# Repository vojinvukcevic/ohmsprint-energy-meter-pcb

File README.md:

# Bluetooth Energy Meter PCB (OhmSprint 2026)

Hardware design of a single-phase **energy meter with Bluetooth Low Energy and USB**, built around the Microchip **ATM90E26** metering IC and an **STM32F373** microcontroller. Designed in **KiCad** by a team for **OhmSprint 2026**, a student hardware competition organized by **Meter&Control** in Belgrade.

**Result:** out of about 40 teams, the design was selected as one of the **10 finalists** whose boards were manufactured and assembled by the organizer. The final stage was board bring-up, firmware testing and verification of measurement accuracy on site.

| PCB layout (F.Cu red, B.Cu blue) | Schematic |
|---|---|
|  | [Open the schematic (PDF)](docs/OhmSprint_V1_schematic.pdf) |

---

## Contents

- [The task](#the-task)
- [My role](#my-role)
- [Hardware architecture](#hardware-architecture)
- [PCB](#pcb)
- [What I would improve in a V2](#what-i-would-improve-in-a-v2)
- [Repository layout](#repository-layout)

---

## The task

Design a device based on the **ATM90E26** metering chip and a microcontroller of our choice that precisely measures:

- RMS voltage and RMS current,
- line frequency,
- instantaneous active power,
- consumed active energy,

and presents the results through an interface of our choice (on-device display, or wired/wireless transfer to a phone or PC).

**Hardware requirements and how the design meets them:**

| Requirement | This design |
|---|---|
| Voltage input: secondary of a mains transformer, approx. 7 V RMS, via a **PJ-002AH-SMT-TR** connector | J1 = PJ-002AH; the same secondary also powers the board (allowed by the task) |
| Current measurement with an **SCT013** current transformer via an **SJ-3523-SMT-TR** connector | J2 = SJ-3523 3.5 mm jack, with burden resistors and an RC anti-aliasing filter |
| Schematic and PCB in **KiCad** | KiCad 10 |
| **2-layer** PCB, max. **15 × 15 cm** | 2 layers, **84.4 × 68.9 mm** |
| Smallest component size **0603** | No part smaller than 0603; most passives are 0805 |
| Organizer's design rules (0.1 mm clearance/track, 0.35 mm min. via, 0.3 mm copper-to-edge, …) | Entered exactly as given in the KiCad board setup, so DRC checks against them |
| Outputs: Gerbers (11 layers), drill files, BOM with MPN and manufacturer | [`fabrication/`](fabrication/), [`bom/`](bom/) |
| Total BOM cost **≤ 50 EUR**, parts from DigiKey | Parts selected from DigiKey |

---

## My role

Team of four: three hardware engineers and one developer who built the phone app.

- **Schematic:** drew almost the entire schematic (power supply, ATM90E26 metering front end, MCU, USB-C and BLE sections).
- **Component selection:** chose the main parts with the team; see [design decisions](#design-decisions).
- **PCB layout:** shared component placement and routing with one teammate.
- **Libraries:** imported and integrated the manufacturer symbols, footprints and 3D models.
- **Fabrication outputs:** generated the Gerber files, drill files and BOM with the team.

---

## Hardware architecture

```mermaid
flowchart LR
    TR["Mains transformer<br/>~7 V AC (J1)"] -->|half-wave rectifier<br/>1N4007 + bulk caps| LDO["AP2213<br/>3.3 V LDO"]
    TR -->|resistor divider| ATM
    CT["SCT013 current<br/>transformer (J2)"] -->|burden + RC filter| ATM["ATM90E26<br/>metering IC"]
    ATM -->|SPI + IRQ, ZX,<br/>WarnOut, CF1/CF2| MCU["STM32F373<br/>MCU"]
    MCU -->|USART2 + RTS/CTS| BLE["BM70<br/>BLE module"]
    MCU -->|USB FS| USB["USB-C<br/>(J3)"]
    LDO --> MCU & ATM & BLE
```

| Block | Part | Notes |
|---|---|---|
| Metering | **ATM90E26** (Microchip) | Required by the task. 8.192 MHz crystal, SPI to the MCU; IRQ, zero-crossing (ZX), WarnOut and energy pulse outputs (CF1/CF2, also drive LEDs) |
| MCU | **STM32F373CCT6** (ST) | Arm Cortex-M4F; SPI master to the ATM90E26, USART2 with hardware flow control to the BLE module, USB full-speed device |
| Wireless | **BM70** (Microchip) | Bluetooth LE module for sending measurements to a phone; copper cutout under the antenna; mode and reset controlled from the MCU |
| Power | **AP2213-3.3** LDO | 3.3 V rail from the half-wave rectified transformer voltage (1N4007, 220 µF + 100 µF bulk) |
| USB | **USB4105** USB-C receptacle, **USBLC6-2SC6** ESD protection | 22 Ω series resistors on D+/D−, 1.5 kΩ D+ pull-up, 5.1 kΩ CC pull-downs (sink) |
| User I/O | 5 slide switches, 4 LEDs | Switches set the ATM90E26 configuration pins, STM32 BOOT0 and the BM70 mode |

Full parts list with manufacturer part numbers: [`bom/OhmSprint_V1_BOM.csv`](bom/OhmSprint_V1_BOM.csv).

### Design decisions

- **STM32F373 as the MCU:** a Cortex-M4 with a hardware floating-point unit for processing the measurement data, from an STM32 line that ST positions for precision analog measurement applications.
- **BM70 for Bluetooth LE:** we chose wireless transfer to a phone as the more challenging option for presenting the results. The BM70 is a complete BLE module controlled over a simple UART interface, so the MCU only needs to send data over serial instead of running a BLE stack.
- **LDO instead of a switching converter:** the board only needs a single 3.3 V rail at low current, so a linear regulator (AP2213) after the rectifier gives a simpler, low-noise supply with fewer parts and no switching layout concerns near the measurement front end.

---

## PCB

| | |
|---|---|
| Layers | 2 (F.Cu, B.Cu) |
| Size | 84.4 × 68.9 mm |
| Thickness | 1.6 mm |
| Ground | GND pour on both layers |
| Mounting | 4 × mounting holes |
| Tool | KiCad 10 |

**Design notes:**
- The BLE module sits at the board edge with a cutout under its antenna, so no copper detunes it.
- The STM32 analog supply (VDDA) is filtered from the 3.3 V rail through a ferrite bead.
- USB data lines run from the connector through the ESD protection IC and the series resistors to the MCU.
- The measurement inputs (transformer and current-transformer jacks) enter on the left edge; the BLE module sits on the opposite edge.

---

## What I would improve in a V2

- **Debug header:** route the STM32 SWD pins (SWDIO, SWCLK) together with NRST and GND to a small header, so the MCU can be programmed and debugged with a standard probe instead of only through the BOOT0 bootloader.
- **Test points:** add test points on the 3.3 V rail, the rectified input and the SPI and UART lines, to make bring-up measurements with an oscilloscope and multimeter faster.
- **USB power:** connect USB-C VBUS so the digital part (MCU, BLE) can be powered and programmed from a laptop without the mains transformer connected.

---

## Repository layout

```
├── README.md
├── kicad/                       # KiCad 10 project
│   ├── OhmSprint_V1.kicad_pro
│   ├── OhmSprint_V1.kicad_sch
│   ├── OhmSprint_V1.kicad_pcb
│   ├── Symbols/                 # imported manufacturer symbols
│   ├── Footprints/              # imported manufacturer footprints
│   └── 3D_models/               # STEP models
├── fabrication/
│   ├── gerbers/                 # Gerber files (2 layers)
│   └── drill/                   # PTH and NPTH drill files
├── bom/OhmSprint_V1_BOM.csv
└── docs/
    ├── OhmSprint_V1_schematic.pdf
    └── img/
        ├── pcb_3d.png           # 3D view of the assembled board
        └── pcb_layout.png       # copper layout, both layers
```

To open the project, install **KiCad 10** and open `kicad/OhmSprint_V1.kicad_pro`.

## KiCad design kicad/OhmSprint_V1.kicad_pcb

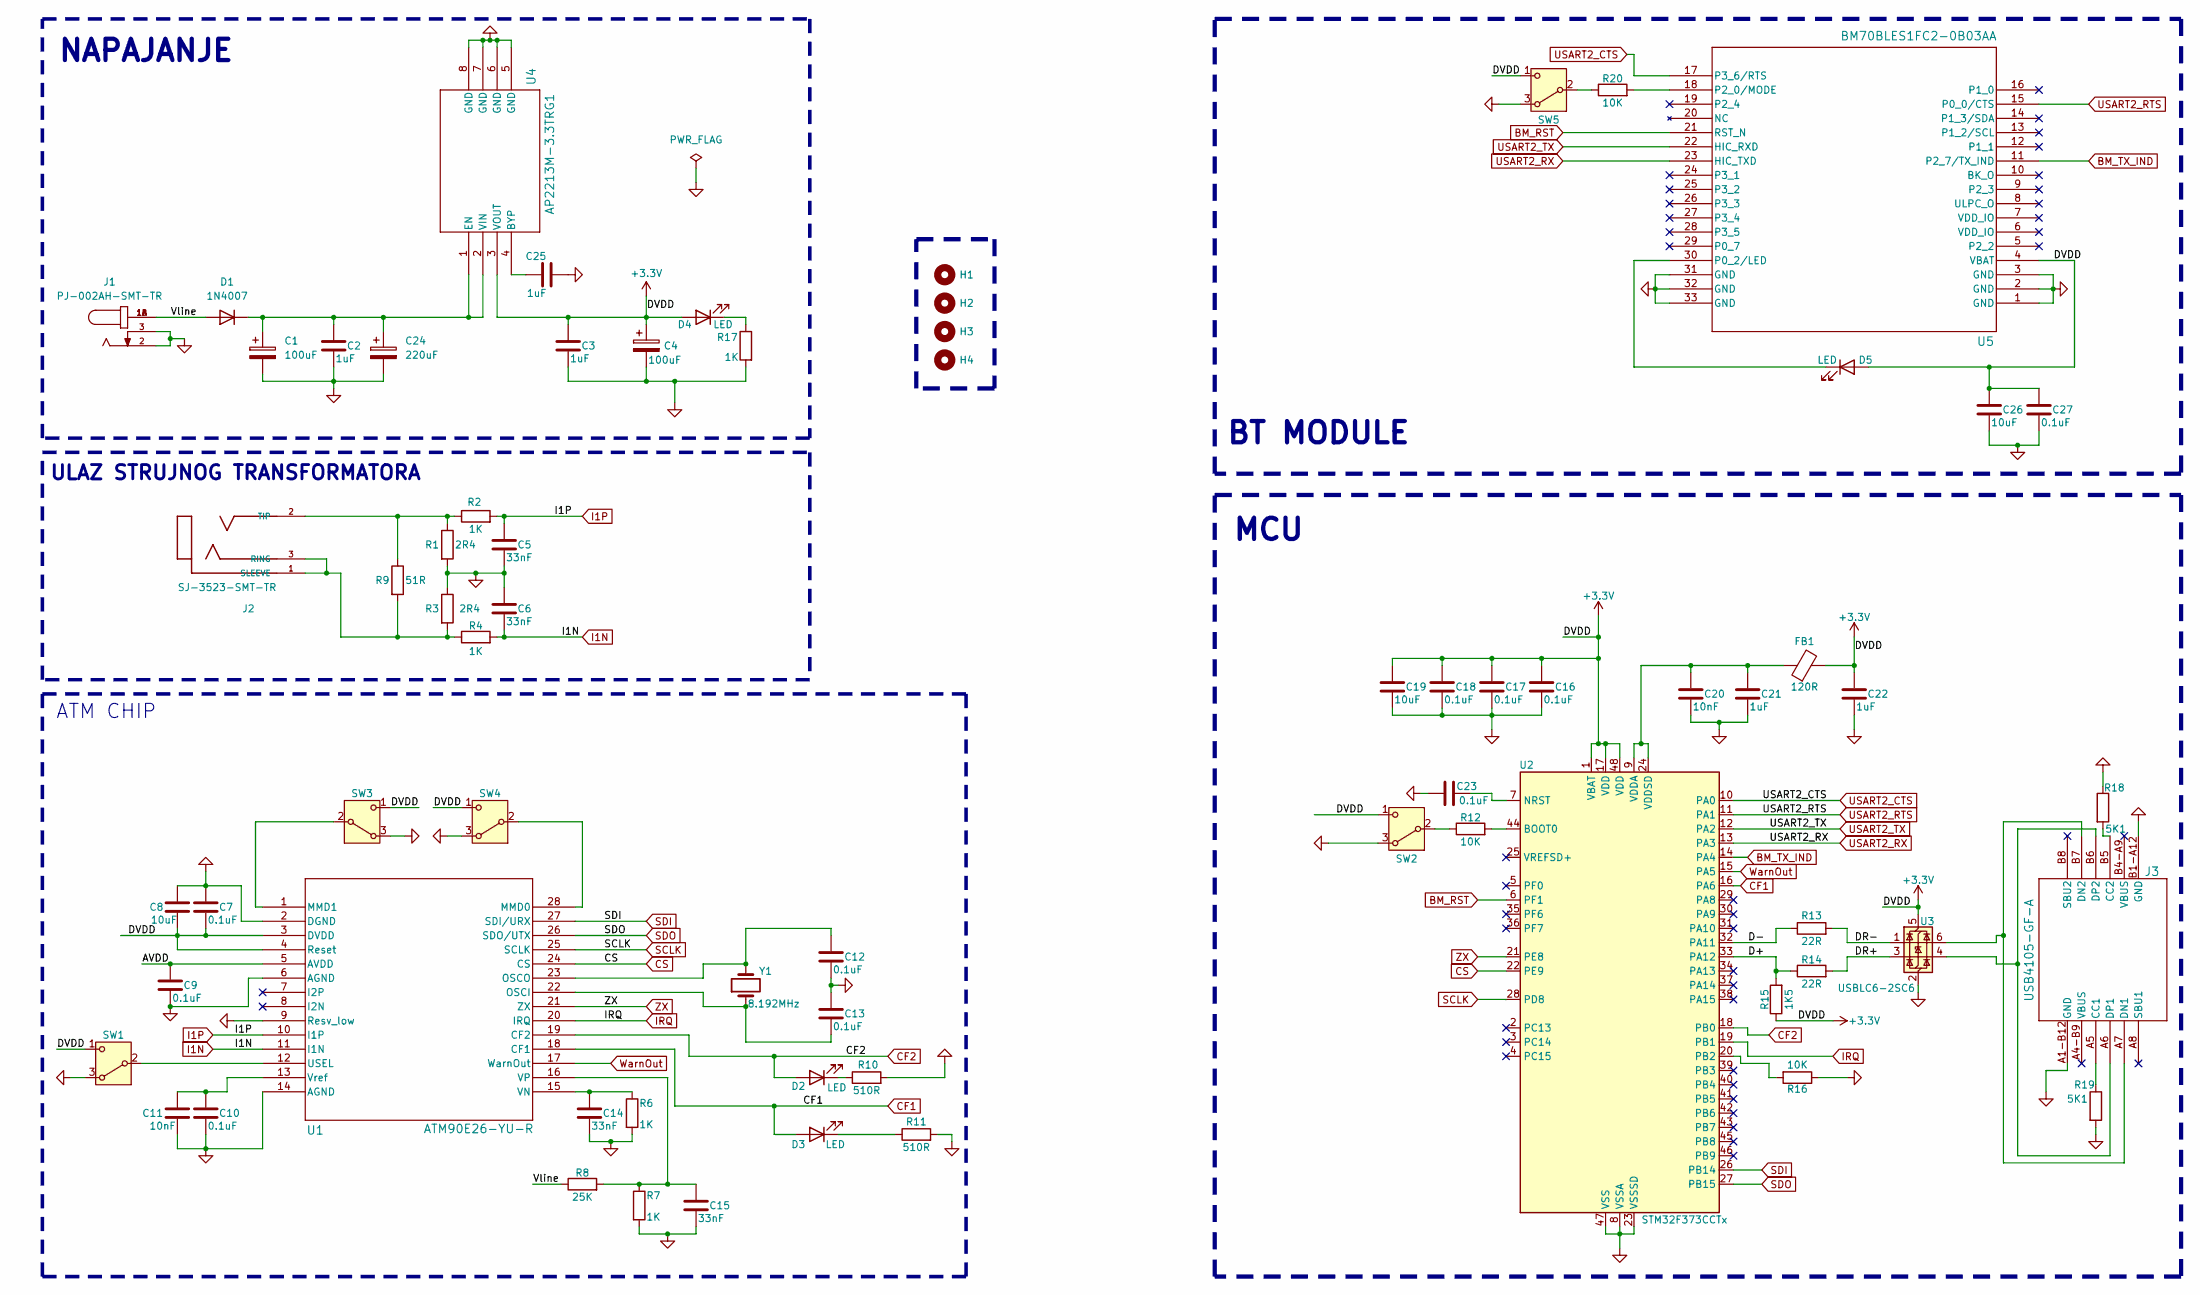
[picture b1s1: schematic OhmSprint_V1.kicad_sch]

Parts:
C1, C4: 100uF; 100uF_Polarized_Cap
C2, C3, C21, C22, C25: 1uF; 1uF_Cap
C5, C6, C14, C15: 33nF; 33nF_Cap
C7, C9, C10, C12, C13, C16, C17, C18, C23, C27: 0.1uF; 0.1uF_Cap
C8, C19, C26: 10uF; 10uF_Cap
C11: 10nF; 10nF_Cap
C20: 10nF; 10uF_Cap
C24: 220uF; 220uF_Polarized_Cap
D1: 1N4007; DIO_N4007-T_DIO
D2, D3, D4, D5: LED; LED_0805_2012Metric
FB1: 120R; FB_LI0805H121R-10
H1, H2, H3, H4: MountingHole; MountingHole_2.1mm
J1: PJ-002AH-SMT-TR; CUI_PJ-002AH-SMT-TR
J2: SJ-3523-SMT-TR; CUI_SJ-3523-SMT-TR
J3: USB4105-GF-A; USB4105_GCT
R1, R3: 2R4; 2R4_Resistor
R2, R4, R6, R7, R17: 1K; 1K_Resistor
R8: 25K; 25K_Resistor
R9: 51R; 51R_Resistor
R10, R11: 510R; 510R_Resistor
R12, R20: 10K; 10K_Resistor
R13, R14: 22R; 22R_Resistor
R15: 1K5; 1K5_Resistor
R16: 10K; 1K5_Resistor
R18, R19: 5K1; 5K1_Resistor
SW1, SW2, SW3, SW4, SW5: SW_Nidec_CAS-120A1; SW_EG1218
U1: ATM90E26-YU-R; ATM90E26
U2: STM32F373CCTx; STM32F373CCT6
U3: USBLC6-2SC6; USBLC6-25C6
U4: AP2213M-3.3TRG1
U5: BM70BLES1FC2-0B03AA; BM70BLES1FC2_MCH
Y1: 8.192MHz; CRYSTAL-AA-8.192MAGE

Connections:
+3.3V: C3.1, C4.1, C7.2, C8.2, C16.1, C17.1, C18.1, C19.1, C22.1, C26.1, C27.1, D4.2 (A), D5.2 (A), FB1.2, R15.1, SW1.1 (C), SW2.1 (C), SW3.1 (C), SW4.1 (C), SW5.1 (C), U1.3 (DVDD), U1.4 (Reset), U2.1 (VBAT), U2.17 (VDD), U2.48 (VDD), U3.5 (VBUS), U4.3 (VOUT), U5.4 (VBAT)
/AVDD: C9.1, U1.5 (AVDD)
/D+: R14.1, R15.2, U2.33 (PA12)
/D-: R13.1, U2.32 (PA11)
/DR+: R14.2, U3.3 (I/O2)
/DR-: R13.2, U3.1 (I/O1)
/Vline: D1.2 (A), J1.1A, J1.1B, R8.1
BM_RST: U2.6 (PF1), U5.21 (RST_N)
BM_TX_IND: U2.14 (PA4), U5.11 (P2_7/TX_IND)
CF1: D3.2 (A), U1.18 (CF1), U2.16 (PA6)
CF2: D2.2 (A), U1.19 (CF2), U2.18 (PB0)
CS: U1.24 (CS), U2.22 (PE9)
GND: C1.2, C2.2, C3.2, C4.2, C5.2, C6.1, C7.1, C8.1, C9.2, C10.2, C11.2, C12.2, C13.1, C14.2, C15.2, C16.2, C17.2, C18.2, C19.2, C20.2, C21.2, C22.2, C23.1, C24.2, C25.2, C26.2, C27.2, J1.2, J1.3, J3.A1-B12 (GND), J3.B1-A12 (GND), R1.2, R3.1, R6.2, R7.2, R10.2, R11.2, R16.1, R17.2, R18.1, R19.2, SW1.3 (A), SW2.3 (A), SW3.3 (A), SW4.3 (A), SW5.3 (A), U1.2 (DGND), U1.6 (AGND), U1.9 (Resv_low), U1.14 (AGND), U2.8 (VSSA), U2.23 (VSSSD), U2.47 (VSS), U3.2 (GND), U4.5 (GND), U4.6 (GND), U4.7 (GND), U4.8 (GND), U5.1 (GND), U5.2 (GND), U5.3 (GND), U5.31 (GND), U5.32 (GND), U5.33 (GND)
I1N: C6.2, R4.2, U1.11 (I1N)
I1P: C5.1, R2.2, U1.10 (I1P)
IRQ: U1.20 (IRQ), U2.19 (PB1)
unnamed: C1.1, C2.1, C24.1, D1.1 (K), U4.1 (EN), U4.2 (VIN)
unnamed: D2.1 (K), R10.1
unnamed: D3.1 (K), R11.1
unnamed: D4.1 (K), R17.1
unnamed: D5.1 (K), U5.30 (P0_2/LED)
unnamed: J2.1 (SLEEVE), J2.3 (RING), R3.2, R4.1, R9.2
unnamed: J2.2 (TIP), R1.1, R2.1, R9.1
unnamed: J3.A5 (CC1), R19.1
unnamed: J3.B5 (CC2), R18.2
unnamed: J3.A7 (DN1), J3.B7 (DN2), U3.6 (I/O1)
unnamed: J3.A6 (DP1), J3.B6 (DP2), U3.4 (I/O2)
unnamed: SW1.2 (B), U1.12 (USEL)
unnamed: R12.1, SW2.2 (B)
unnamed: SW3.2 (B), U1.1 (MMD1)
unnamed: SW4.2 (B), U1.28 (MMD0)
unnamed: R20.1, SW5.2 (B)
unnamed: C13.2, U1.22 (OSCI), Y1.1
unnamed: C12.1, U1.23 (OSCO), Y1.2
unnamed: C14.1, R6.1, U1.15 (VN)
unnamed: C15.1, R7.1, R8.2, U1.16 (VP)
unnamed: C10.1, C11.1, U1.13 (Vref)
unnamed: R12.2, U2.44 (BOOT0)
unnamed: C23.2, U2.7 (NRST)
unnamed: R16.2, U2.20 (PB2)
unnamed: C20.1, C21.1, FB1.1, U2.9 (VDDA), U2.24 (VDDSD)
unnamed: C25.1, U4.4 (BYP)
unnamed: R20.2, U5.18 (P2_0/MODE)
SCLK: U1.25 (SCLK), U2.28 (PD8)
SDI: U1.27 (SDI/URX), U2.26 (PB14)
SDO: U1.26 (SDO/UTX), U2.27 (PB15)
USART2_CTS: U2.10 (PA0), U5.17 (P3_6/RTS)
USART2_RTS: U2.11 (PA1), U5.15 (P0_0/CTS)
USART2_RX: U2.13 (PA3), U5.23 (HIC_TXD)
USART2_TX: U2.12 (PA2), U5.22 (HIC_RXD)
WarnOut: U1.17 (WarnOut), U2.15 (PA5)
ZX: U1.21 (ZX), U2.21 (PE8)

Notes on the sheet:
NAPAJANJE
ATM CHIP
BT MODULE
ULAZ STRUJNOG TRANSFORMATORA
MCU

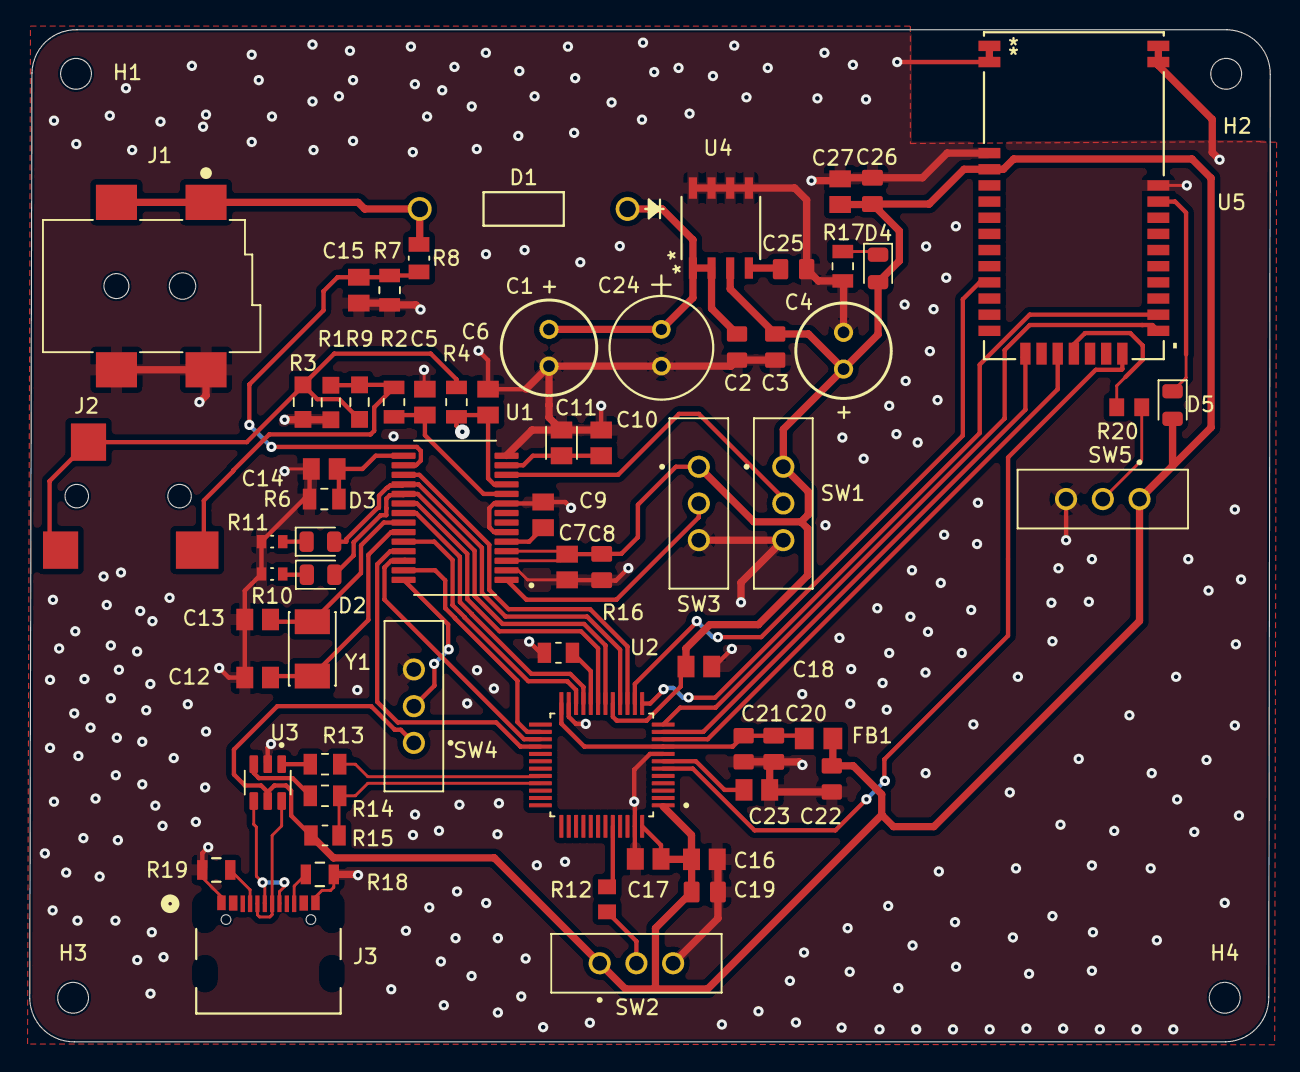
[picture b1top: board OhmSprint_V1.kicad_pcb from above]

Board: 2 copper layers, 84.4 x 68.9 mm, 70 parts (0 on the bottom side), 52 nets.

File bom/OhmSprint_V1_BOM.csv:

"Reference","Qty","Value","Exclude from BOM","Datasheet","MANUFACTURER","Manufacturer Product Number"
"C1,C4","2","100uF","","https://www.digikey.com/en/products/detail/w%C3%BCrth-elektr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","Würth Elektronik","860040573004"
"C2,C3,C21,C22,C25","5","1uF","","https://www.digikey.com/en/products/detail/samsung-electro-m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","Samsung Electro-Mechanics","CL21B105KAFNNNE"
"C5,C6,C14,C15","4","33nF","","https://www.digikey.com/en/products/detail/tdk/C2012C0G1H333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","TDK","C2012C0G1H333J125AA"
"C7,C9,C10,C12,C13,C16,C17,C18,C23,C27","10","0.1uF","","https://www.digikey.com/en/products/detail/kemet/C0805C104K5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","KEMET","C0805C104K5RACTU"
"C8,C19,C26","3","10uF","","https://www.digikey.com/en/products/detail/samsung-electro-m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","Samsung Electro-Mechanics","CL21A106KOQNNNE"
"C11,C20","2","10nF","","https://www.digikey.com/en/products/detail/kemet/C0805C103K5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","KEMET","C0805C103K5RACTU"
"C24","1","220uF","","https://www.digikey.com/en/products/detail/rubycon/25YXJ220M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","Rubycon","25YXJ220M6.3X11"
"D1","1","1N4007","","https://www.digikey.com/en/products/detail/mcc-micro-commerc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","MCC (Micro Commercial Components)","1N4007-TP"
"D2,D3,D4,D5","4","LED","","https://www.digikey.com/en/products/detail/xinglight/XL-2012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","XINGLIGHT","XL-2012UGC"
"FB1","1","120R","","https://www.digikey.com/en/products/detail/laird-signal-inte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","Laird-Signal Integrity Products","LI0805H121R-10"
"J1","1","PJ-002AH-SMT-TR","","https://www.digikey.com/en/products/detail/same-sky-formerly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","Same Sky (Formerly CUI Devices)","PJ-002AH-SMT-TR"
"J2","1","SJ-3523-SMT-TR","","https://www.digikey.com/en/products/detail/same-sky-formerly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","Same Sky (Formerly CUI Devices)","SJ-3523-SMT-TR"
"J3","1","USB4105-GF-A","","https://www.digikey.com/en/products/detail/gct/USB4105-GF-A/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","GCT","USB4105-GF-A"
"R1,R3","2","2R4","","https://www.digikey.com/en/products/detail/panasonic-industr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","Panasonic Industry","ERJ-6GEYJ2R4V"
"R2,R4,R6,R7,R17","5","1K","","https://www.digikey.com/en/products/detail/vishay-dale/CRCW0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","Vishay Dale","CRCW08051K00FKEA"
"R8","1","25K","","https://www.digikey.com/en/products/detail/te-connectivity-p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","TE Connectivity Passive Product","CPF0805B25KE1"
"R9","1","51R","","https://www.digikey.com/en/products/detail/panasonic-industr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","Panasonic Industry","ERJ-P06F51R0V"
"R10,R11","2","510R","","https://www.digikey.com/en/products/detail/panasonic-industr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","Panasonic Industry","ERJ-3GEYJ511V"
"R12,R16,R20,R21","4","10K","","https://www.digikey.com/en/products/detail/yageo/RT0805BRD07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","YAGEO","RT0805BRD0710KL"
"R13,R14","2","22R","","https://www.digikey.com/en/products/detail/vishay-dale/CRCW0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","Vishay Dale","CRCW080522R0FKEA"
"R15","1","1K5","","https://www.digikey.com/en/products/detail/yageo/RC0805FR-07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","YAGEO","RC0805FR-071K5L"
"R18,R19","2","5K1","","https://www.digikey.com/en/products/detail/koa-speer-electro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","KOA Speer Electronics, Inc.","RK73B2ATTD512J"
"SW1,SW2,SW3,SW4,SW5","5","SW_Nidec_CAS-120A1","","https://www.digikey.com/en/products/detail/e-switch/EG1218/101726","E-Switch","EG1218"
"U1","1","ATM90E26-YU-R","","https://www.digikey.com/en/products/detail/microchip-technol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","Microchip Technology","ATM90E26-YU-R"
"U2","1","STM32F373CCTx","","https://www.digikey.com/en/products/detail/stmicroelectronic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","STMicroelectronics","STM32F373CCT6"
"U3","1","USBLC6-2SC6","","https://www.digikey.com/en/products/detail/stmicroelectronic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","STMicroelectronics","USBLC6-2SC6"
"U4","1","AP2213M-3.3TRG1","","https://www.digikey.com/en/products/detail/diodes-incorporat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","Diodes Incorporated","AP2213M-3.3TRG1"
"U5","1","BM70BLES1FC2-0B03AA","","https://www.digikey.com/en/products/detail/microchip-technol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","Microchip Technology ","BM70BLES1FC2-0B03AA"
"Y1","1","8.192MHz","","https://www.digikey.com/en/products/detail/txc-corporation/A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","TXC CORPORATION","AA-8.192MAGE-T"
